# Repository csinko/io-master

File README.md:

# io-master
Dominate the I/O!

## Subsystems Overviews

### [GUI](https://github.com/csinko/io-master/wiki/GUI-Subsystem)
The purpose of the GUI interface is to create a user friendly yet customizable program to help users tell the micro-controller to use whatever protocols that the user wishes to use from the provided list. The interface will include drop down menus to adjust the protocol that the board will use.  This interface will also allow the user to select what information they want to send through the device as well as start and stop the flow of information through the device. The GUI will also define the hardware pins and clock speeds needed to run whichever protocol is selected. This includes setting the voltage levels that the board will expect to see. This will define what is seen as a 1 or a 0. The gui will most likely be done using python. Possible challenges include figuring out which GUI base to use in python. Possible options are appJar, TkInter, PyQT, or Kivy. More research will be done on each to figure out which one is best suited for this project. 

### [MCU Firmware](https://github.com/csinko/io-master/wiki/MCU-Firmware-Subsystem)
The MCU is responsible for reading and writing the logic. Firmware will need to be designed to load in data from the computer, connect it to the corresponding DMA register that routes to the correct output, and stream data as it comes in. Likewise, the firmware will also need to read in data over the DMA, and transfer it to send to the computer when appropriate. Strict scheduling and context switching will need to be designed in order to ensure smooth operation at high frequencies. Other contexts will need to be considered, such as reading from one set of I/O and writing to another set, or recording logic data read in to an SD card.

### [MCU Power and Interface](https://github.com/csinko/io-master/wiki/MCU-Power-and-Interface-Subsystem)
MCU Power and Interface is responsible for receiving configuration and executing commands. These commands will come through the serial bus and need to be parsed/decoded. Execution will include adjusting the clock speed, target voltage levels, and re-configuring pins as specified by the commands received.

These capabilities will be crucial for switching between protocols on the multi-use pins. The challenges will be primarily with creating a good control scheme for managing all the necessary multiplexers to route signals to all the proper pins, at the correct speed and voltages.

### [I/O Level Shifting and Logic](https://github.com/csinko/io-master/wiki/IO-Level-Shifting-and-Logic-Subsystem)
The Level Shifting and Logic Subsystem is responsible for providing electrical conversion between the microcontroller interface and the device under test. This includes acting as an output and input to the microcontroller, providing logic-high, logic-low, and floating output states, bidirectional logic-level conversion, and capability to drive/receive differential or single-ended lines. This block should be fully configurable via control signals from the microcontroller. This includes setting the high and low voltages, optional pull-up/pull-down resistors, and multiplexing the line between single-ended and differential hardware. Design challenges include implementing a bidirectional differential transceiver and ensuring that multiplexing does not affect high speed operation.

### [Circuit Protection](https://github.com/csinko/io-master/wiki/Circuit-Protection-Subsystem)
Circuit protection is a crucial part of any device to help safeguard against unexpected and unplanned power issues. This is important to prevent injury to users, damage to the device and potentially fire. This will include having fuses, diodes, conformal coating, reverse polarity protection, over voltage protection and will protect against accidental grounding.
Some challenges that may occur is due to the learning curve of designing the circuit protection circuit. Designing a circuit that can account for over voltage protection, short circuit protection, reverse polarity protection, etc and maintain a small footprint on a circuit board could prove to be difficult. Accounting for different/higher voltage levels used by the different protocols may become a challenge.

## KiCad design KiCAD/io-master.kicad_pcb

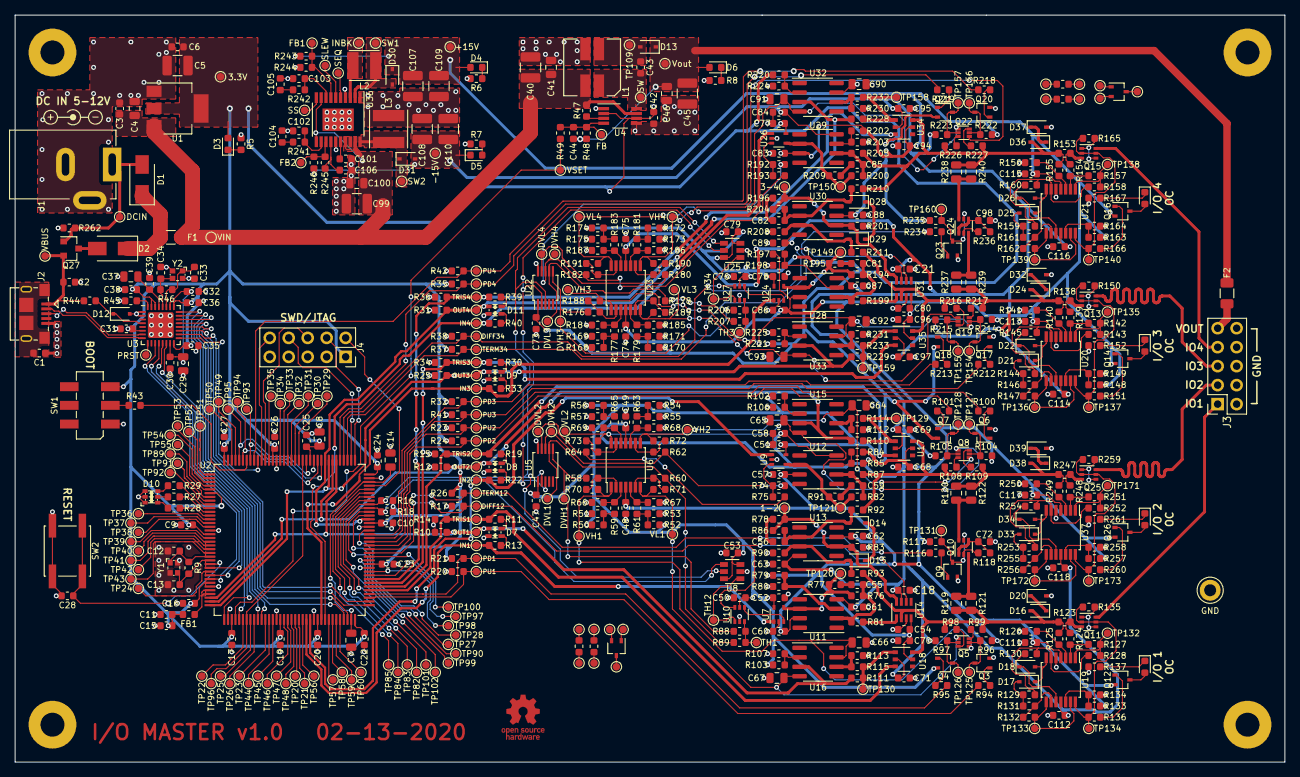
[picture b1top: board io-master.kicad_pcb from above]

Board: 4 copper layers, 170.0 x 100.0 mm, 671 parts (0 on the bottom side), 377 nets.

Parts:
C1: 0.47u; C_0603_1608Metric
C2, C10, C11, C43, C101, C106: 1u; C_0603_1608Metric
C3, C6, C9, C15, C16, C17, C18, C19, C20, C21, C22, C23, C24, C25, C26, C27, C28, C30, C31, C32, C35, C36, C38, C39, C42, C47, C48, C49, C50, C51, C52, C53, C54, C57, C58, C60, C61, C62, C63, C68, C69, C70, C71, C73, C74, C75, C76, C77, C78, C79, C80, C83, C84, C86, C87, C88, C89, C94, C95, C96, C97, C111, C112, C113, C114, C115, C116, C117, C118: 0.1u; C_0603_1608Metric
C4, C41, C46, C64, C65, C66, C67, C90, C91, C92, C93, C100: 10u; C_0805_2012Metric
C5, C107, C108: 22u; C_1210_3225Metric
C7, C14: 2.2u; C_0805_2012Metric
C8, C29, C37: 4.7u; C_0805_2012Metric
C12, C13, C33, C34: 20p; C_0603_1608Metric
C40, C45, C99, C109, C110: C; C_1210_3225Metric
C44: 33p; C_0603_1608Metric
C55, C56, C59, C81, C82, C85, C102, C103: C; C_0603_1608Metric
C72, C98: 1000p; C_0603_1608Metric
C104: 0.22u; C_0603_1608Metric
C105: 82p; C_0603_1608Metric
D1, D2: B130L; D_SMA
D3: ORANGE; LED_0603_1608Metric
D4, D5: BLUE; LED_0603_1608Metric
D6: GREEN; LED_0603_1608Metric
D7, D8, D9, D11: YEL/GRN; LED_Kingbright_APTB1615YSGC
D10: RGB; LED_Everlight_19-337C
D12: DDZ5V6ASF; D_SOD-323F
D13, D30, D31: NSR0530HT1G; D_SOD-323
D14, D15, D28, D29: MM3Z9V1ST1G; D_SOD-323
D16, D20, D24, D32, D36, D37, D38, D39: MM3Z15VST1G; D_SOD-323
D17, D18, D21, D22, D25, D26, D33, D34: 1N4148; D_SOD-323
D19, D23, D27, D35: RED; LED_0603_1608Metric
F1: 0.5A; Fuse_1206_3216Metric
F2: 0.1A; Fuse_1206_3216Metric
FB1: MZ1608-102Y; R_0603_1608Metric
H1, H2, H3, H4: M3; MountingHole_3.2mm_M3_Pad
J1: 54-00166; BarrelJack_Tensility_54-00166_Horizontal
J2: 10118193; USB_Micro-B_Amphenol_10118193-0001LF_Horizontal
J3: 0.1" HDR; PinSocket_2x05_P2.54mm_Vertical_AltNumbering
J4: 0.1" HDR; PinSocket_2x05_P2.54mm_Vertical
L1: 82u; L_Bourns_SRF0703
L2: 10u; L_Abracon_ASPI-0418FS
L3: 15u; L_Taiyo-Yuden_NR-50xx
Q1, Q2: Q_NPN_BCE; SOT-323_SC-70
Q3, Q6, Q9, Q17, Q20, Q23: MMBT3904; SOT-323_SC-70
Q4, Q7, Q12, Q14, Q16, Q18, Q21, Q26: MMBT3906; SOT-323_SC-70
Q5, Q8, Q19, Q22: DMG1029SV; SOT-563
Q10, Q11, Q13, Q15, Q24, Q25: DMN63D8LDW; SOT-363_SC-70-6
Q27: DMP3099L; SOT-23
R1, R2, R3, R4, R9, R77, R78, R91, R195, R196, R209: R; R_0603_1608Metric
R5, R11, R13, R19, R22, R30, R33, R39, R40: 1K; R_0603_1608Metric
R6, R7, R43, R49, R94, R95, R98, R99, R100, R101, R108, R109, R116, R124, R125, R136, R137, R139, R140, R151, R152, R154, R155, R166, R167, R212, R213, R216, R217, R218, R219, R226, R227, R234, R248, R249, R260, R261: 10K; R_0603_1608Metric
R8, R16, R18: 4.7K; R_0603_1608Metric
R10, R12, R14, R15, R17, R20, R21, R23, R24, R25, R26, R31, R32, R34, R35, R36, R37, R38, R41, R42, R50, R51, R52, R53, R54, R55, R56, R57, R74, R75, R83, R88, R89, R96, R97, R102, R103, R104, R105, R106, R107, R112, R113, R117, R118, R126, R127, R128, R129, R130, R131, R132, R133, R135, R141, R142, R143, R144, R145, R146, R147, R148, R150, R156, R157, R158, R159, R160, R161, R162, R163, R165, R168, R169, R170, R171, R172, R173, R174, R175, R192, R193, R201, R206, R207, R214, R215, R220, R221, R222, R223, R224, R225, R230, R231, R235, R236, R250, R251, R252, R253, R254, R255, R256, R257, R259, R262: 100K; R_0603_1608Metric
R27, R28, R29: 330; R_0603_1608Metric
R44: 820; R_0603_1608Metric
R45: 12K; R_0603_1608Metric
R46, R66, R67, R68, R69, R70, R71, R72, R73, R79, R81, R84, R87, R184, R185, R186, R187, R188, R189, R190, R191, R197, R199, R202, R205: 1M; R_0603_1608Metric
R47: 220K; R_0603_1608Metric
R48, R58, R59, R60, R61, R62, R63, R64, R65, R76, R80, R82, R85, R176, R177, R178, R179, R180, R181, R182, R183, R194, R198, R200, R203: 110K; R_0603_1608Metric
R86, R90, R92, R93, R204, R208, R210, R211: 47K; R_0603_1608Metric
R110, R111, R114, R115, R228, R229, R232, R233: 0; R_0603_1608Metric
R119, R120, R121, R122, R237, R238, R239, R240: 120; R_0805_2012Metric
R123, R138, R153, R247: 2; R_0603_1608Metric
R134, R149, R164, R258: 6.8K; R_0603_1608Metric
R241: 5.36K; R_0603_1608Metric
R242: 390K; R_0603_1608Metric
R243: 2.43M; R_0603_1608Metric
R244: 137K; R_0603_1608Metric
R245: 118K; R_0603_1608Metric
R246: 2.32M; R_0603_1608Metric
SW1: JS202011SCQN; SW_DPDT_CK_JS202011SCQN
SW2: EVQ-Q2B03W; SW_SPST_EVQQ2
TP1, TP2, TP3, TP5, TP6, TP7, TP8, TP9, TP10, TP11, TP12, TP13, TP14, TP15, TP109, TP120, TP121, TP125, TP126, TP127, TP128, TP129, TP130, TP131, TP132, TP133, TP134, TP135, TP136, TP137, TP138, TP139, TP140, TP149, TP150, TP154, TP155, TP156, TP157, TP158, TP159, TP160, TP171, TP172, TP173: TestPoint; TestPoint_Pad_D1.0mm
TP4: GND; TestPoint_Keystone_5010-5014_Multipurpose
TP16: VIN; TestPoint_Pad_D1.0mm
TP17: DCIN; TestPoint_Pad_D1.0mm
TP18: VBUS; TestPoint_Pad_D1.0mm
TP19: 3.3V; TestPoint_Pad_D1.0mm
TP20: PU5; TestPoint_Pad_D1.0mm
TP21: PD5; TestPoint_Pad_D1.0mm
TP22: PU6; TestPoint_Pad_D1.0mm
TP23: PD6; TestPoint_Pad_D1.0mm
TP24: PU7; TestPoint_Pad_D1.0mm
TP25: PD7; TestPoint_Pad_D1.0mm
TP26: PU8; TestPoint_Pad_D1.0mm
TP27: PD8; TestPoint_Pad_D1.0mm
TP28: PG8; TestPoint_Pad_D1.0mm
TP29: PG9; TestPoint_Pad_D1.0mm
TP30: PG10; TestPoint_Pad_D1.0mm
TP31: PG11; TestPoint_Pad_D1.0mm
TP32: PG12; TestPoint_Pad_D1.0mm
TP33: PG13; TestPoint_Pad_D1.0mm
TP34: PG14; TestPoint_Pad_D1.0mm
TP35: PG15; TestPoint_Pad_D1.0mm
TP36: PF3; TestPoint_Pad_D1.0mm
TP37: PF4; TestPoint_Pad_D1.0mm
TP38: PF5; TestPoint_Pad_D1.0mm
TP39: PF6; TestPoint_Pad_D1.0mm
TP40: PF7; TestPoint_Pad_D1.0mm
TP41: PF8; TestPoint_Pad_D1.0mm
TP42: PF9; TestPoint_Pad_D1.0mm
TP43: PF10; TestPoint_Pad_D1.0mm
TP44: PF11; TestPoint_Pad_D1.0mm
TP45: PF12; TestPoint_Pad_D1.0mm
TP46: PF13; TestPoint_Pad_D1.0mm
TP47: PF14; TestPoint_Pad_D1.0mm
TP48: PF15; TestPoint_Pad_D1.0mm
TP49: PE0; TestPoint_Pad_D1.0mm
TP50: PE1; TestPoint_Pad_D1.0mm
TP51: PE2; TestPoint_Pad_D1.0mm
TP52: PE3; TestPoint_Pad_D1.0mm
TP53: PE4; TestPoint_Pad_D1.0mm
TP54: PE5; TestPoint_Pad_D1.0mm
TP55: PE6; TestPoint_Pad_D1.0mm
TP56: PE7; TestPoint_Pad_D1.0mm
TP57: PE12; TestPoint_Pad_D1.0mm
TP58: PE13; TestPoint_Pad_D1.0mm
TP59: PE14; TestPoint_Pad_D1.0mm
TP60: PE15; TestPoint_Pad_D1.0mm
TP61: OUT1; TestPoint_Pad_D1.0mm
TP62: OUT2; TestPoint_Pad_D1.0mm
TP63: OUT3; TestPoint_Pad_D1.0mm
TP64: OUT4; TestPoint_Pad_D1.0mm
TP65: IN1; TestPoint_Pad_D1.0mm
TP66: IN2; TestPoint_Pad_D1.0mm
TP67: IN3; TestPoint_Pad_D1.0mm
TP68: IN4; TestPoint_Pad_D1.0mm
TP69: TRIS1; TestPoint_Pad_D1.0mm
TP70: TRIS2; TestPoint_Pad_D1.0mm
TP71: TRIS3; TestPoint_Pad_D1.0mm
TP72: TRIS4; TestPoint_Pad_D1.0mm
TP73: DIFF12; TestPoint_Pad_D1.0mm
TP74: TERM12; TestPoint_Pad_D1.0mm
TP75: DIFF34; TestPoint_Pad_D1.0mm
TP76: TERM34; TestPoint_Pad_D1.0mm
TP77: PU1; TestPoint_Pad_D1.0mm
TP78: PU2; TestPoint_Pad_D1.0mm
TP79: PU3; TestPoint_Pad_D1.0mm
TP80: PU4; TestPoint_Pad_D1.0mm
TP82: TXO; TestPoint_Pad_D1.0mm
TP83: RXI; TestPoint_Pad_D1.0mm
TP84: DM; TestPoint_Pad_D1.0mm
TP85: DP; TestPoint_Pad_D1.0mm
TP89: DIFF78; TestPoint_Pad_D1.0mm
TP90: TERM78; TestPoint_Pad_D1.0mm
TP91: DIFF56; TestPoint_Pad_D1.0mm
TP92: TERM56; TestPoint_Pad_D1.0mm
TP93: OUT5; TestPoint_Pad_D1.0mm
TP94: OUT6; TestPoint_Pad_D1.0mm
TP95: OUT7; TestPoint_Pad_D1.0mm
TP96: OUT8; TestPoint_Pad_D1.0mm
TP97: TRIS5; TestPoint_Pad_D1.0mm
TP98: TRIS6; TestPoint_Pad_D1.0mm
TP99: TRIS7; TestPoint_Pad_D1.0mm
TP100: TRIS8; TestPoint_Pad_D1.0mm
TP101: SCL; TestPoint_Pad_D1.0mm
TP102: SDA; TestPoint_Pad_D1.0mm
TP103: VSET; TestPoint_Pad_D1.0mm
TP104: PD1; TestPoint_Pad_D1.0mm
TP105: PD2; TestPoint_Pad_D1.0mm
TP106: PD3; TestPoint_Pad_D1.0mm
TP107: PD4; TestPoint_Pad_D1.0mm
TP108: SW; TestPoint_Pad_D1.0mm
TP110: FB; TestPoint_Pad_D1.0mm
TP111: Vout; TestPoint_Pad_D1.0mm
TP112: DVH1; TestPoint_Pad_D1.0mm
TP113: DVL1; TestPoint_Pad_D1.0mm
TP114: DVH2; TestPoint_Pad_D1.0mm
TP115: DVL2; TestPoint_Pad_D1.0mm
TP116: VH1; TestPoint_Pad_D1.0mm
TP117: VL1; TestPoint_Pad_D1.0mm
TP118: VH2; TestPoint_Pad_D1.0mm
TP119: VL2; TestPoint_Pad_D1.0mm
TP122: TH12; TestPoint_Pad_D1.0mm
TP123: 1-2; TestPoint_Pad_D1.0mm
TP124: TH1; TestPoint_Pad_D1.0mm
TP141: DVH3; TestPoint_Pad_D1.0mm
TP142: DVL3; TestPoint_Pad_D1.0mm
TP143: DVH4; TestPoint_Pad_D1.0mm
TP144: DVL4; TestPoint_Pad_D1.0mm
TP145: VH3; TestPoint_Pad_D1.0mm
TP146: VL3; TestPoint_Pad_D1.0mm
TP147: VH4; TestPoint_Pad_D1.0mm
TP148: VL4; TestPoint_Pad_D1.0mm
TP151: TH34; TestPoint_Pad_D1.0mm
TP152: 3-4; TestPoint_Pad_D1.0mm
TP153: TH3; TestPoint_Pad_D1.0mm
TP161: SS; TestPoint_Pad_D1.0mm
TP162: SLEW; TestPoint_Pad_D1.0mm
TP163: SEQ; TestPoint_Pad_D1.0mm
TP164: INBK; TestPoint_Pad_D1.0mm
TP165: SW2; TestPoint_Pad_D1.0mm
TP166: SW1; TestPoint_Pad_D1.0mm
TP167: FB1; TestPoint_Pad_D1.0mm
TP168: FB2; TestPoint_Pad_D1.0mm
TP169: +15V; TestPoint_Pad_D1.0mm
TP170: -15V; TestPoint_Pad_D1.0mm
TP174: PRST; TestPoint_Pad_D1.0mm
U1: AZ1117-3.3; SOT-223-3_TabPin2
U2: STM32H743ZITx; LQFP-144_20x20mm_P0.5mm
U3: USB3300-EZK; QFN-32-1EP_5x5mm_P0.5mm_EP3.45x3.45mm
U4: LM2621; VSSOP-8_3.0x3.0mm_P0.65mm
U5: MCP4728A0; MSOP-10_3x3mm_P0.5mm
U6, U19, U20, U21, U23, U37: NCV20074; TSSOP-14_4.4x5mm_P0.65mm
U7, U9, U24, U26: TS3011; SOT-353_SC-70-5
U8: MCP4725A0; SOT-23-6
U10, U27: PI5A3157; SOT-363_SC-70-6
U11, U12, U13, U15, U16, U28, U29, U30, U32, U33: LM7171; SOIC-8_3.9x4.9mm_P1.27mm
U14, U31: DG449; SOT-23-8
U17, U18, U34, U35: DG448DV; TSOP-6_1.65x3.05mm_P0.95mm
U22: MCP4728A2; MSOP-10_3x3mm_P0.5mm
U25: MCP4725A1; SOT-23-6
U36: ADP5070AREZ; ETSSOP-20-1EP_4.4x6.5mm_P0.65mm_EP3x4.2mm
Y1: 48MHz; Crystal_SMD_Murata_XRCGB
Y2: 24MHz; Crystal_SMD_Murata_XRCGB

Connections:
/3.3V: C5.1, C6.1, C8.1, C9.1, C10.1, C11.1, C15.1, C16.1, C17.1, C19.1, C20.1, C22.1, C23.1, C24.1, C25.1, C26.1, C27.1, C31.1, C35.1, C36.1, C38.1, C42.1, C47.1, C50.1, C51.1, C52.1, C53.1, C73.1, C76.1, C77.1, C78.1, C79.1, D3.2, FB1.1, J4.1, Q4.2, Q7.2, Q18.2, Q21.2, R16.1, R18.1, R21.1, R24.1, R26.1, R32.1, R35.1, R37.1, R50.1, R52.1, R54.1, R56.1, R102.2, R103.2, R168.1, R170.1, R172.1, R174.1, R220.2, R221.2, SW1.3, TP19.1, U1.2, U2.6, U2.17, U2.30, U2.39, U2.52, U2.62, U2.72, U2.84, U2.95, U2.108, U2.121, U2.131, U2.144, U3.6, U3.16, U3.25, U3.30, U3.31, U4.2, U4.6, U5.1, U7.5, U8.3, U8.6, U9.5, U10.5, U22.1, U24.5, U25.3, U25.6, U26.5, U27.5
/+15V: C48.1, C54.1, C57.1, C60.1, C62.1, C68.1, C70.1, C74.1, C80.1, C83.1, C86.1, C88.1, C94.1, C96.1, C107.1, C109.1, C111.1, C113.1, C115.1, C117.1, D4.2, D30.1, Q12.2, Q14.2, Q16.2, Q26.2, R79.2, R84.2, R96.1, R104.1, R117.1, R133.1, R148.1, R163.1, R197.2, R202.2, R214.1, R222.1, R235.1, R243.1, R257.1, TP169.1, U6.4, U11.7, U12.7, U13.7, U14.4, U17.5, U18.5, U19.4, U20.4, U21.4, U23.4, U28.7, U29.7, U30.7, U31.4, U34.5, U35.5, U37.4
/-15V: C18.2, C21.2, C49.2, C58.2, C61.2, C63.2, C69.2, C71.2, C75.2, C84.2, C87.2, C89.2, C95.2, C97.2, C108.2, C110.2, C112.2, C114.2, C116.2, C118.2, D5.1, D31.2, R97.2, R105.2, R215.2, R223.2, R246.2, TP170.1, U6.11, U11.4, U12.4, U13.4, U14.7, U17.2, U18.2, U19.11, U20.11, U21.11, U23.11, U28.4, U29.4, U30.4, U31.7, U34.2, U35.2, U37.11
/Adjustable Regulator/SETPOINT: R49.2, TP103.1, U2.40
/Circuit Protection - I/O Pin 1/IO_1: D16.2, R93.1, R98.2, R99.1, R119.1, R121.1, R123.2, R125.2, U14.2, U18.6
/Circuit Protection - I/O Pin 1/TARGET_IO_1: J3.1, Q11.6
/Circuit Protection - I/O Pin 2/IO_2: D38.2, R87.2, R92.1, R108.2, R109.1, R120.2, R122.2, R247.2, R249.2, U17.6
/Circuit Protection - I/O Pin 2/TARGET_IO_2: J3.2, Q25.6
/Circuit Protection - I/O Pin 3/IO_3: D24.2, R138.2, R140.2, R211.1, R216.2, R217.1, R237.1, R239.1, U31.2, U35.6
/Circuit Protection - I/O Pin 3/TARGET_IO_3: J3.3, Q13.6
/Circuit Protection - I/O Pin 4/IO_4: D36.2, R153.2, R155.2, R205.2, R210.1, R226.2, R227.1, R238.2, R240.2, U34.6
/Circuit Protection - I/O Pin 4/TARGET_IO_4: J3.4, Q15.6
/D+: J2.3, U3.7
/D-: J2.2, U3.8
/Level Shifter - I/O Pins 1&2/CMP1+: R76.1, R77.1, TP120.1, U7.4, U11.6
/Level Shifter - I/O Pins 1&2/CMP1-: C55.1, R76.2, R81.1, U11.2
/Level Shifter - I/O Pins 1&2/CMP2+: R82.1, R91.1, TP121.1, U9.4, U12.6
/Level Shifter - I/O Pins 1&2/CMP2-: C59.1, R82.2, R87.1, U12.2
/Level Shifter - I/O Pins 1&2/CMP+: R78.1, R83.1, R86.2, TP123.1, U13.6, U14.8
/Level Shifter - I/O Pins 1&2/CMP-: C56.1, D14.2, R86.1, R92.2, U13.2
/Level Shifter - I/O Pins 1&2/DAC_VH1: R58.2, R88.2, TP112.1, U5.6
/Level Shifter - I/O Pins 1&2/DAC_VH2: R62.2, R74.2, TP114.1, U5.8
/Level Shifter - I/O Pins 1&2/DAC_VL1: R60.2, R89.1, TP113.1, U5.7
/Level Shifter - I/O Pins 1&2/DAC_VL2: R64.2, R75.1, TP115.1, U5.9
/Level Shifter - I/O Pins 1&2/I2C_SCL: R16.2, TP101.1, U2.100, U5.2, U8.5, U22.2, U25.5
/Level Shifter - I/O Pins 1&2/I2C_SDA: R18.2, TP102.1, U2.99, U5.3, U8.4, U22.3, U25.4
/Level Shifter - I/O Pins 1&2/IO_1&2_DIFF: R17.1, TP73.1, U2.87, U10.6, U14.6
/Level Shifter - I/O Pins 1&2/IO_1&2_TH: TP122.1, U8.1, U10.1
/Level Shifter - I/O Pins 1&2/IO_1_IN: R13.1, TP65.1, U2.59, U7.1
/Level Shifter - I/O Pins 1&2/IO_1_OUT: D7.2, R10.1, R111.2, TP61.1, U2.34, U2.114, U16.3
/Level Shifter - I/O Pins 1&2/IO_1_PU: R20.1, R94.2, TP77.1, U2.75
/Level Shifter - I/O Pins 1&2/IO_1_TH: R88.1, R89.2, TP124.1, U10.3
/Level Shifter - I/O Pins 1&2/IO_2_IN: R22.1, TP66.1, U2.60, U9.1
/Level Shifter - I/O Pins 1&2/IO_2_OUT: D8.2, R12.1, R110.2, TP62.1, U2.35, U2.115, U15.3
/Level Shifter - I/O Pins 1&2/IO_2_PU: R23.1, R100.2, TP78.1, U2.90
/Level Shifter - I/O Pins 1&2/VH1: C66.1, Q5.4, R70.1, TP116.1, U6.1, U16.7
/Level Shifter - I/O Pins 1&2/VH2: C64.1, Q8.4, R72.1, TP118.1, U6.8, U15.7
/Level Shifter - I/O Pins 1&2/VL1: C67.2, Q5.1, R71.1, TP117.1, U6.7, U16.4
/Level Shifter - I/O Pins 1&2/VL2: C65.2, Q8.1, R73.1, TP119.1, U6.14, U15.4
/Level Shifter - I/O Pins 1&2/~IO_1&2_TERM: R26.2, R116.2, TP74.1, U2.88
/Level Shifter - I/O Pins 1&2/~IO_1_PD: R21.2, R95.2, TP104.1, U2.76
/Level Shifter - I/O Pins 1&2/~IO_1_TRIS: R11.1, R14.1, TP69.1, U2.77, U18.3
/Level Shifter - I/O Pins 1&2/~IO_2_PD: R24.2, R101.2, TP105.1, U2.89
/Level Shifter - I/O Pins 1&2/~IO_2_TRIS: R15.1, R19.1, TP70.1, U2.78, U17.3
/Level Shifter - I/O Pins 3&4/CMP3+: R194.1, R195.1, TP149.1, U24.4, U28.6
/Level Shifter - I/O Pins 3&4/CMP3-: C81.1, R194.2, R199.1, U28.2
/Level Shifter - I/O Pins 3&4/CMP4+: R200.1, R209.1, TP150.1, U26.4, U29.6
/Level Shifter - I/O Pins 3&4/CMP4-: C85.1, R200.2, R205.1, U29.2
/Level Shifter - I/O Pins 3&4/CMP+: R196.1, R201.1, R204.2, TP152.1, U30.6, U31.8
/Level Shifter - I/O Pins 3&4/CMP-: C82.1, D28.2, R204.1, R210.2, U30.2
/Level Shifter - I/O Pins 3&4/DAC_VH3: R176.2, R206.2, TP141.1, U22.6
/Level Shifter - I/O Pins 3&4/DAC_VH4: R180.2, R192.2, TP143.1, U22.8
/Level Shifter - I/O Pins 3&4/DAC_VL3: R178.2, R207.1, TP142.1, U22.7
/Level Shifter - I/O Pins 3&4/DAC_VL4: R182.2, R193.1, TP144.1, U22.9
/Level Shifter - I/O Pins 3&4/IO_3&4_DIFF: R38.1, TP75.1, U2.112, U27.6, U31.6
/Level Shifter - I/O Pins 3&4/IO_3&4_TH: TP151.1, U25.1, U27.1
/Level Shifter - I/O Pins 3&4/IO_3_IN: R33.1, TP67.1, U2.63, U24.1
/Level Shifter - I/O Pins 3&4/IO_3_OUT: D9.2, R25.1, R229.2, TP63.1, U2.36, U2.116, U33.3
/Level Shifter - I/O Pins 3&4/IO_3_PU: R41.1, R212.2, TP79.1, U2.91
/Level Shifter - I/O Pins 3&4/IO_3_TH: R206.1, R207.2, TP153.1, U27.3
/Level Shifter - I/O Pins 3&4/IO_4_IN: R40.1, TP68.1, U2.64, U26.1
/Level Shifter - I/O Pins 3&4/IO_4_OUT: D11.2, R31.1, R228.2, TP64.1, U2.96, U2.117, U32.3
/Level Shifter - I/O Pins 3&4/IO_4_PU: R42.1, R218.2, TP80.1, U2.136
/Level Shifter - I/O Pins 3&4/VH3: C92.1, Q19.4, R188.1, TP145.1, U23.1, U33.7
/Level Shifter - I/O Pins 3&4/VH4: C90.1, Q22.4, R190.1, TP147.1, U23.8, U32.7
/Level Shifter - I/O Pins 3&4/VL3: C93.2, Q19.1, R189.1, TP146.1, U23.7, U33.4
/Level Shifter - I/O Pins 3&4/VL4: C91.2, Q22.1, R191.1, TP148.1, U23.14, U32.4
/Level Shifter - I/O Pins 3&4/~IO_3&4_TERM: R37.2, R234.2, TP76.1, U2.111
/Level Shifter - I/O Pins 3&4/~IO_3_PD: R32.2, R213.2, TP106.1, U2.92
/Level Shifter - I/O Pins 3&4/~IO_3_TRIS: R30.1, R34.1, TP71.1, U2.79, U35.3
/Level Shifter - I/O Pins 3&4/~IO_4_PD: R35.2, R219.2, TP107.1, U2.113
/Level Shifter - I/O Pins 3&4/~IO_4_TRIS: R36.1, R39.1, TP72.1, U2.80, U34.3
/Microcontroller/IO_5&6_DIFF: TP91.1, U2.8
/Microcontroller/IO_5_IN: TP57.1, U2.65
/Microcontroller/IO_5_OUT: TP93.1, U2.118, U2.137
/Microcontroller/IO_5_PU: TP20.1, U2.56
/Microcontroller/IO_6_IN: TP58.1, U2.66
/Microcontroller/IO_6_OUT: TP94.1, U2.119, U2.139
/Microcontroller/IO_6_PU: TP22.1, U2.42
/Microcontroller/IO_7&8_DIFF: TP89.1, U2.7
/Microcontroller/IO_7_IN: TP59.1, U2.67
/Microcontroller/IO_7_OUT: TP95.1, U2.122, U2.140
/Microcontroller/IO_7_PU: TP24.1, U2.27
/Microcontroller/IO_8_IN: TP60.1, U2.68
/Microcontroller/IO_8_OUT: TP96.1, U2.43, U2.123
/Microcontroller/IO_8_PU: TP26.1, U2.45
/Microcontroller/OSC_IN: C13.1, R9.2, U2.24, Y1.3
/Microcontroller/OSC_OUT: C12.1, R9.1, U2.23, Y1.1
/Microcontroller/STATUS_B: R29.1, U2.10
/Microcontroller/STATUS_G: R28.1, U2.12
/Microcontroller/STATUS_R: R27.1, U2.11
/Microcontroller/TCK_SWDCLK: J4.4, U2.109
/Microcontroller/TDI: J4.8, U2.110
/Microcontroller/TDO_SWO: J4.6, U2.133
/Microcontroller/TMS_SWDIO: J4.2, U2.105
/Microcontroller/UART_RXI: TP83.1, U2.102
/Microcontroller/UART_TXO: TP82.1, U2.101
/Microcontroller/ULPI_CK: U2.41, U3.14
/Microcontroller/ULPI_D0: U2.37, U3.24
/Microcontroller/ULPI_D1: U2.46, U3.23
/Microcontroller/ULPI_D2: U2.47, U3.22
/Microcontroller/ULPI_D3: U2.69, U3.21
/Microcontroller/ULPI_D4: U2.70, U3.20
/Microcontroller/ULPI_D5: U2.73, U3.19
/Microcontroller/ULPI_D6: U2.74, U3.18
/Microcontroller/ULPI_D7: U2.135, U3.17
/Microcontroller/ULPI_DIR: U2.28, U3.12
/Microcontroller/ULPI_NXT: U2.29, U3.11
/Microcontroller/ULPI_STP: U2.26, U3.13
/Microcontroller/USB_FS_DM: TP84.1, U2.103
/Microcontroller/USB_FS_DP: TP85.1, U2.104
/Microcontroller/USB_VBUS: C2.1, J2.1, Q27.2, R44.2, TP18.1
/Microcontroller/VCAP: C7.1, C14.1, U2.71, U2.106
/Microcontroller/VDD1.8: C29.1, C30.1, C32.1, U3.15, U3.26
/Microcontroller/VDDA: FB1.2, U2.32, U2.33
/Microcontroller/VDDA1.8: C37.1, C39.1, U3.29
/Microcontroller/XI: C34.1, R46.2, U3.28, Y2.3
/Microcontroller/XO: C33.1, R46.1, U3.27, Y2.1
/Microcontroller/nRESET: J4.10, U2.134
/Microcontroller/~IO_5&6_TERM: TP92.1, U2.9
/Microcontroller/~IO_5_PD: TP21.1, U2.57
/Microcontroller/~IO_5_TRIS: TP97.1, U2.81
/Microcontroller/~IO_6_PD: TP23.1, U2.48
/Microcontroller/~IO_6_TRIS: TP98.1, U2.82
/Microcontroller/~IO_7&8_TERM: TP90.1, U2.98
/Microcontroller/~IO_7_PD: TP25.1, U2.44
/Microcontroller/~IO_7_TRIS: TP99.1, U2.85
/Microcontroller/~IO_8_PD: TP27.1, U2.97
/Microcontroller/~IO_8_TRIS: TP100.1, U2.86
/Vin: C3.1, C4.1, C40.1, C41.1, C99.1, C100.1, F1.1, L1.2, R47.1, TP16.1, U1.3, U4.7, U36.9, U36.11, U36.17, U36.18, U36.19
/Vout: C44.1, C45.1, C46.1, D6.2, D13.1, F2.1, R48.1, TP111.1
CHASSIS: C1.2, H1.1, H2.1, H3.1, H4.1, J2.6
GND: C1.1, C2.2, C3.2, C4.2, C5.2, C6.2, C7.2, C8.2, C9.2, C10.2, C11.2, C12.2, C13.2, C14.2, C15.2, C16.2, C17.2, C18.1, C19.2, C20.2, C21.1, C22.2, C23.2, C24.2, C25.2, C26.2, C27.2, C28.2, C29.2, C30.2, C31.2, C32.2, C33.2, C34.2, C35.2, C36.2, C37.2, C38.2, C39.2, C40.2, C41.2, C42.2, C45.2, C46.2, C47.2, C48.2, C49.1, C50.2, C51.2, C52.2, C53.2, C54.2, C57.2, C58.1, C60.2, C61.1, C62.2, C63.1, C64.2, C65.1, C66.2, C67.1, C68.2, C69.1, C70.2, C71.1, C72.1, C73.2, C74.2, C75.1, C76.2, C77.2, C78.2, C79.2, C80.2, C83.2, C84.1, C86.2, C87.1, C88.2, C89.1, C90.2, C91.1, C92.2, C93.1, C94.2, C95.1, C96.2, C97.1, C98.1, C99.2, C100.2, C101.2, C102.2, C103.2, C104.1, C105.1, C106.2, C107.2, C108.1, C109.2, C110.1, C111.2, C112.1, C113.2, C114.1, C115.2, C116.1, C117.2, C118.1, D7.4, D8.4, D9.4, D10.1, D10.3, D10.5, D11.4, D12.2, D20.2, D32.2, D37.2, D39.2, J1.2, J1.3, J2.5, J3.6, J3.7, J3.8, J3.9, J3.10, J4.3, J4.5, J4.9, L1.4, L3.2, Q3.2, Q6.2, Q9.2, Q17.2, Q20.2, Q23.2, R5.2, R6.2, R7.2, R8.2, R10.2, R12.2, R14.2, R15.2, R17.2, R20.2, R23.2, R25.2, R31.2, R34.2, R36.2, R38.2, R41.2, R42.2, R45.2, R51.2, R53.2, R55.2, R57.2, R66.1, R67.1, R68.1, R69.1, R80.1, R83.2, R85.1, R90.2, R106.2, R107.2, R112.2, R113.2, R126.2, R134.2, R137.2, R141.2, R149.2, R152.2, R156.2, R164.2, R167.2, R169.2, R171.2, R173.2, R175.2, R184.1, R185.1, R186.1, R187.1, R198.1, R201.2, R203.1, R208.2, R224.2, R225.2, R230.2, R231.2, R244.2, R250.2, R258.2, R261.2, R262.2, SW1.1, SW2.1, TP4.1, U1.1, U2.16, U2.31, U2.38, U2.51, U2.61, U2.83, U2.94, U2.107, U2.120, U2.130, U3.1, U3.2, U3.33, U4.1, U4.5, U5.10, U7.2, U8.2, U9.2, U10.2, U14.3, U19.5, U20.5, U21.5, U22.10, U24.2, U25.2, U26.2, U27.2, U31.3, U36.1, U36.4, U36.15, U36.21, U37.5, Y1.2, Y1.4, Y2.2, Y2.4
unnamed: C28.1, SW2.2, U2.25
unnamed: C43.1, D13.2, L1.3, TP109.1
unnamed: C43.2, L1.1, TP108.1, U4.8
unnamed: C44.2, R48.2, R49.1, TP110.1, U4.4
unnamed: C55.2, R77.2
unnamed: C56.2, R78.2
unnamed: C59.2, R91.2
unnamed: C72.2, Q10.1, Q10.4, R118.1
unnamed: C81.2, R195.2
unnamed: C82.2, R196.2
unnamed: C85.2, R209.2
unnamed: C98.2, Q24.1, Q24.4, R236.1
unnamed: C101.1, U36.16
unnamed: C102.1, R241.2, U36.12
unnamed: C103.1, R242.2, U36.8
unnamed: C104.2, R241.1
unnamed: C105.2, R242.1
unnamed: C106.1, R245.1, U36.14
unnamed: D1.1, D2.1, F1.2
unnamed: D1.2, J1.1, Q27.1, R262.1, TP17.1
unnamed: D2.2, Q27.3
unnamed: D3.1, R5.1
unnamed: D4.1, R6.1
unnamed: D5.2, R7.1
unnamed: D6.1, R8.1
unnamed: D7.1, R11.2
unnamed: D7.3, R13.2
unnamed: D8.1, R19.2
unnamed: D8.3, R22.2
unnamed: D9.1, R30.2
unnamed: D9.3, R33.2
unnamed: D10.2, R28.2
unnamed: D10.4, R27.2
unnamed: D10.6, R29.2
unnamed: D11.1, R39.2
unnamed: D11.3, R40.2
unnamed: D12.1, R44.1, U3.4
unnamed: D14.1, D15.1
unnamed: D15.2, R90.1, R93.2, U13.3
unnamed: D16.1, D20.1
unnamed: D17.1, D18.2, U19.7
unnamed: D17.2, R129.1, R131.2
unnamed: D18.1, R130.1, U19.10
unnamed: D19.1, R137.1
unnamed: D19.2, Q12.3
unnamed: D21.1, D22.2, U20.7
unnamed: D21.2, R144.1, R146.2
unnamed: D22.1, R145.1, U20.10
unnamed: D23.1, R152.1
unnamed: D23.2, Q14.3
unnamed: D24.1, D32.1
unnamed: D25.1, D26.2, U21.7
unnamed: D25.2, R159.1, R161.2
unnamed: D26.1, R160.1, U21.10
unnamed: D27.1, R167.1
unnamed: D27.2, Q16.3
unnamed: D28.1, D29.1
unnamed: D29.2, R208.1, R211.2, U30.3
unnamed: D30.2, L2.2, TP166.1, U36.2
unnamed: D31.1, L3.1, TP165.1, U36.20
unnamed: D33.1, D34.2, U37.7
unnamed: D33.2, R253.1, R255.2
unnamed: D34.1, R254.1, U37.10
unnamed: D35.1, R261.1
unnamed: D35.2, Q26.3
unnamed: D36.1, D37.1
unnamed: D38.1, D39.1
unnamed: F2.2, J3.5
unnamed: L2.1, TP164.1, U36.3
unnamed: Q1.1, TP3.1
unnamed: Q1.2, TP7.1
unnamed: Q1.3, TP8.1
unnamed: Q2.1, TP11.1
unnamed: Q2.2, TP14.1
unnamed: Q2.3, TP15.1
unnamed: Q3.1, R94.1
unnamed: Q3.3, Q5.5, R96.2, TP125.1
unnamed: Q4.1, R95.1
unnamed: Q4.3, Q5.2, R97.1, TP126.1
unnamed: Q5.3, R98.1
unnamed: Q5.6, R99.2
unnamed: Q6.1, R100.1
unnamed: Q6.3, Q8.5, R104.2, TP127.1
unnamed: Q7.1, R101.1
unnamed: Q7.3, Q8.2, R105.1, TP128.1
unnamed: Q8.3, R108.1
unnamed: Q8.6, R109.2
unnamed: Q9.1, R116.1
unnamed: Q9.3, Q10.2, Q10.5, R117.2, R118.2, TP131.1
unnamed: Q10.3, R119.2, R121.2
unnamed: Q10.6, R120.1, R122.1
unnamed: Q11.1, Q11.4, R135.1
unnamed: Q11.2, Q11.5, R135.2, R136.2, TP134.1, U19.14
unnamed: Q11.3, R123.1, R124.2
unnamed: Q12.1, R136.1
unnamed: Q13.1, Q13.4, R150.1
unnamed: Q13.2, Q13.5, R150.2, R151.2, TP137.1, U20.14
unnamed: Q13.3, R138.1, R139.2
unnamed: Q14.1, R151.1
unnamed: Q15.1, Q15.4, R165.1
unnamed: Q15.2, Q15.5, R165.2, R166.2, TP140.1, U21.14
unnamed: Q15.3, R153.1, R154.2
unnamed: Q16.1, R166.1
unnamed: Q17.1, R212.1
unnamed: Q17.3, Q19.5, R214.2, TP154.1
unnamed: Q18.1, R213.1
unnamed: Q18.3, Q19.2, R215.1, TP155.1
unnamed: Q19.3, R216.1
unnamed: Q19.6, R217.2
unnamed: Q20.1, R218.1
unnamed: Q20.3, Q22.5, R222.2, TP156.1
unnamed: Q21.1, R219.1
unnamed: Q21.3, Q22.2, R223.1, TP157.1
unnamed: Q22.3, R226.1
unnamed: Q22.6, R227.2
unnamed: Q23.1, R234.1
unnamed: Q23.3, Q24.2, Q24.5, R235.2, R236.2, TP160.1
unnamed: Q24.3, R237.2, R239.2
unnamed: Q24.6, R238.1, R240.1
unnamed: Q25.1, Q25.4, R259.1
unnamed: Q25.2, Q25.5, R259.2, R260.2, TP173.1, U37.14
unnamed: Q25.3, R247.1, R248.2
unnamed: Q26.1, R260.1
unnamed: R1.1, TP1.1
unnamed: R1.2, TP2.1
unnamed: R2.1, TP5.1
unnamed: R2.2, TP6.1
unnamed: R3.1, TP9.1
unnamed: R3.2, TP10.1
unnamed: R4.1, TP12.1
unnamed: R4.2, TP13.1
unnamed: R43.1, U2.138
unnamed: R43.2, SW1.2
unnamed: R45.1, U3.32
unnamed: R47.2, U4.3
unnamed: R50.2, R51.1, R59.2
unnamed: R52.2, R53.1, R61.2
unnamed: R54.2, R55.1, R63.2
unnamed: R56.2, R57.1, R65.2
unnamed: R58.1, R70.2, U6.2
unnamed: R59.1, R66.2, U6.3
unnamed: R60.1, R71.2, U6.6
unnamed: R61.1, R67.2, U6.5
unnamed: R62.1, R72.2, U6.9
unnamed: R63.1, R68.2, U6.10
unnamed: R64.1, R73.2, U6.13
unnamed: R65.1, R69.2, U6.12
unnamed: R74.1, R75.2, U9.3
unnamed: R79.1, R80.2, U11.3
unnamed: R81.2, U14.1
unnamed: R84.1, R85.2, U12.3
unnamed: R102.1, R106.1, U15.2
unnamed: R103.1, R107.1, U16.2
unnamed: R110.1, R114.1, TP129.1, U17.1
unnamed: R111.1, R115.1, TP130.1, U18.1
unnamed: R112.1, R114.2, U15.6
unnamed: R113.1, R115.2, U16.6
unnamed: R124.1, R127.2, U19.2
unnamed: R125.1, R126.1, U19.3
unnamed: R127.1, R128.2, TP132.1, U19.1
unnamed: R128.1, R129.2, R130.2, U19.6
unnamed: R131.1, R132.2, U19.9
unnamed: R132.1, TP133.1, U19.8, U19.13
unnamed: R133.2, R134.1, U19.12
unnamed: R139.1, R142.2, U20.2
unnamed: R140.1, R141.1, U20.3
unnamed: R142.1, R143.2, TP135.1, U20.1
unnamed: R143.1, R144.2, R145.2, U20.6
unnamed: R146.1, R147.2, U20.9
unnamed: R147.1, TP136.1, U20.8, U20.13
unnamed: R148.2, R149.1, U20.12
unnamed: R154.1, R157.2, U21.2
unnamed: R155.1, R156.1, U21.3
unnamed: R157.1, R158.2, TP138.1, U21.1
unnamed: R158.1, R159.2, R160.2, U21.6
unnamed: R161.1, R162.2, U21.9
unnamed: R162.1, TP139.1, U21.8, U21.13
unnamed: R163.2, R164.1, U21.12
unnamed: R168.2, R169.1, R177.2
unnamed: R170.2, R171.1, R179.2
unnamed: R172.2, R173.1, R181.2
unnamed: R174.2, R175.1, R183.2
unnamed: R176.1, R188.2, U23.2
unnamed: R177.1, R184.2, U23.3
unnamed: R178.1, R189.2, U23.6
unnamed: R179.1, R185.2, U23.5
unnamed: R180.1, R190.2, U23.9
unnamed: R181.1, R186.2, U23.10
unnamed: R182.1, R191.2, U23.13
unnamed: R183.1, R187.2, U23.12
unnamed: R192.1, R193.2, U26.3
unnamed: R197.1, R198.2, U28.3
unnamed: R199.2, U31.1
unnamed: R202.1, R203.2, U29.3
unnamed: R220.1, R224.1, U32.2
unnamed: R221.1, R225.1, U33.2
unnamed: R228.1, R232.1, TP158.1, U34.1
unnamed: R229.1, R233.1, TP159.1, U35.1
unnamed: R230.1, R232.2, U32.6
unnamed: R231.1, R233.2, U33.6
unnamed: R243.2, R244.1, TP167.1, U36.7
unnamed: R245.2, R246.1, TP168.1, U36.13
unnamed: R248.1, R251.2, U37.2
unnamed: R249.1, R250.1, U37.3
unnamed: R251.1, R252.2, TP171.1, U37.1
unnamed: R252.1, R253.2, R254.2, U37.6
unnamed: R255.1, R256.2, U37.9
unnamed: R256.1, TP172.1, U37.8, U37.13
unnamed: R257.2, R258.1, U37.12
unnamed: TP28.1, U2.93
unnamed: TP29.1, U2.124
unnamed: TP30.1, U2.125
unnamed: TP31.1, U2.126
unnamed: TP32.1, U2.127
unnamed: TP33.1, U2.128
unnamed: TP34.1, U2.129
unnamed: TP35.1, U2.132
unnamed: TP36.1, U2.13
unnamed: TP37.1, U2.14
unnamed: TP38.1, U2.15
unnamed: TP39.1, U2.18
unnamed: TP40.1, U2.19
unnamed: TP41.1, U2.20
unnamed: TP42.1, U2.21
unnamed: TP43.1, U2.22
unnamed: TP44.1, U2.49
unnamed: TP45.1, U2.50
unnamed: TP46.1, U2.53
unnamed: TP47.1, U2.54
unnamed: TP48.1, U2.55
unnamed: TP49.1, U2.141
unnamed: TP50.1, U2.142
unnamed: TP51.1, U2.1
unnamed: TP52.1, U2.2
unnamed: TP53.1, U2.3
unnamed: TP54.1, U2.4
unnamed: TP55.1, U2.5
unnamed: TP56.1, U2.58
unnamed: TP161.1, U36.10
unnamed: TP162.1, U36.6
unnamed: TP163.1, U36.5
unnamed: TP174.1, U3.9
unnamed: U7.3, U10.4
unnamed: U24.3, U27.4
